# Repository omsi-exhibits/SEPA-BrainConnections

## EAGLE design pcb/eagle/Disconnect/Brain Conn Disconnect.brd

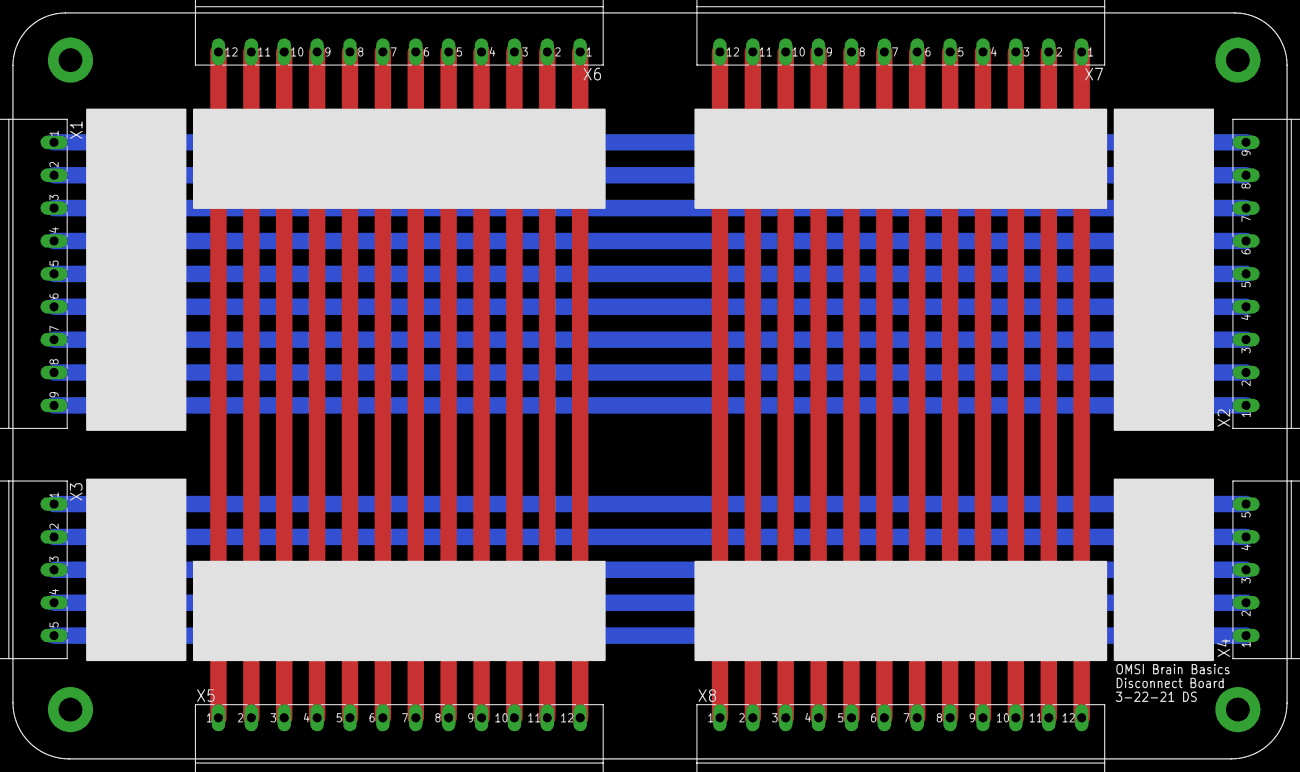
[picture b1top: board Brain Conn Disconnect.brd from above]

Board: 2 copper layers, 196.8 x 115.2 mm, 12 parts (0 on the bottom side), 38 nets.

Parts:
S1, S2, S3, S4: STANDOFF_ELECTRICAL144; STANDOFF_ELECTRICAL_144MILL_NORMAL_SCREW
X1, X2: MSTBA9
X3, X4: MSTBA5
X5, X6, X7, X8: MSTBA12

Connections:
unnamed: X3.1, X4.5
unnamed: X3.2, X4.4
unnamed: X3.3, X4.3
unnamed: X3.4, X4.2
unnamed: X3.5, X4.1
unnamed: X1.1, X2.9
unnamed: X1.2, X2.8
unnamed: X1.3, X2.7
unnamed: X1.4, X2.6
unnamed: X1.5, X2.5
unnamed: X1.6, X2.4
unnamed: X1.7, X2.3
unnamed: X1.8, X2.2
unnamed: X1.9, X2.1
unnamed: X5.12, X6.1
unnamed: X5.11, X6.2
unnamed: X5.10, X6.3
unnamed: X5.9, X6.4
unnamed: X5.8, X6.5
unnamed: X5.7, X6.6
unnamed: X5.6, X6.7
unnamed: X5.5, X6.8
unnamed: X5.4, X6.9
unnamed: X5.3, X6.10
unnamed: X5.2, X6.11
unnamed: X5.1, X6.12
unnamed: X7.1, X8.12
unnamed: X7.2, X8.11
unnamed: X7.3, X8.10
unnamed: X7.4, X8.9
unnamed: X7.5, X8.8
unnamed: X7.6, X8.7
unnamed: X7.7, X8.6
unnamed: X7.8, X8.5
unnamed: X7.9, X8.4
unnamed: X7.10, X8.3
unnamed: X7.11, X8.2
unnamed: X7.12, X8.1

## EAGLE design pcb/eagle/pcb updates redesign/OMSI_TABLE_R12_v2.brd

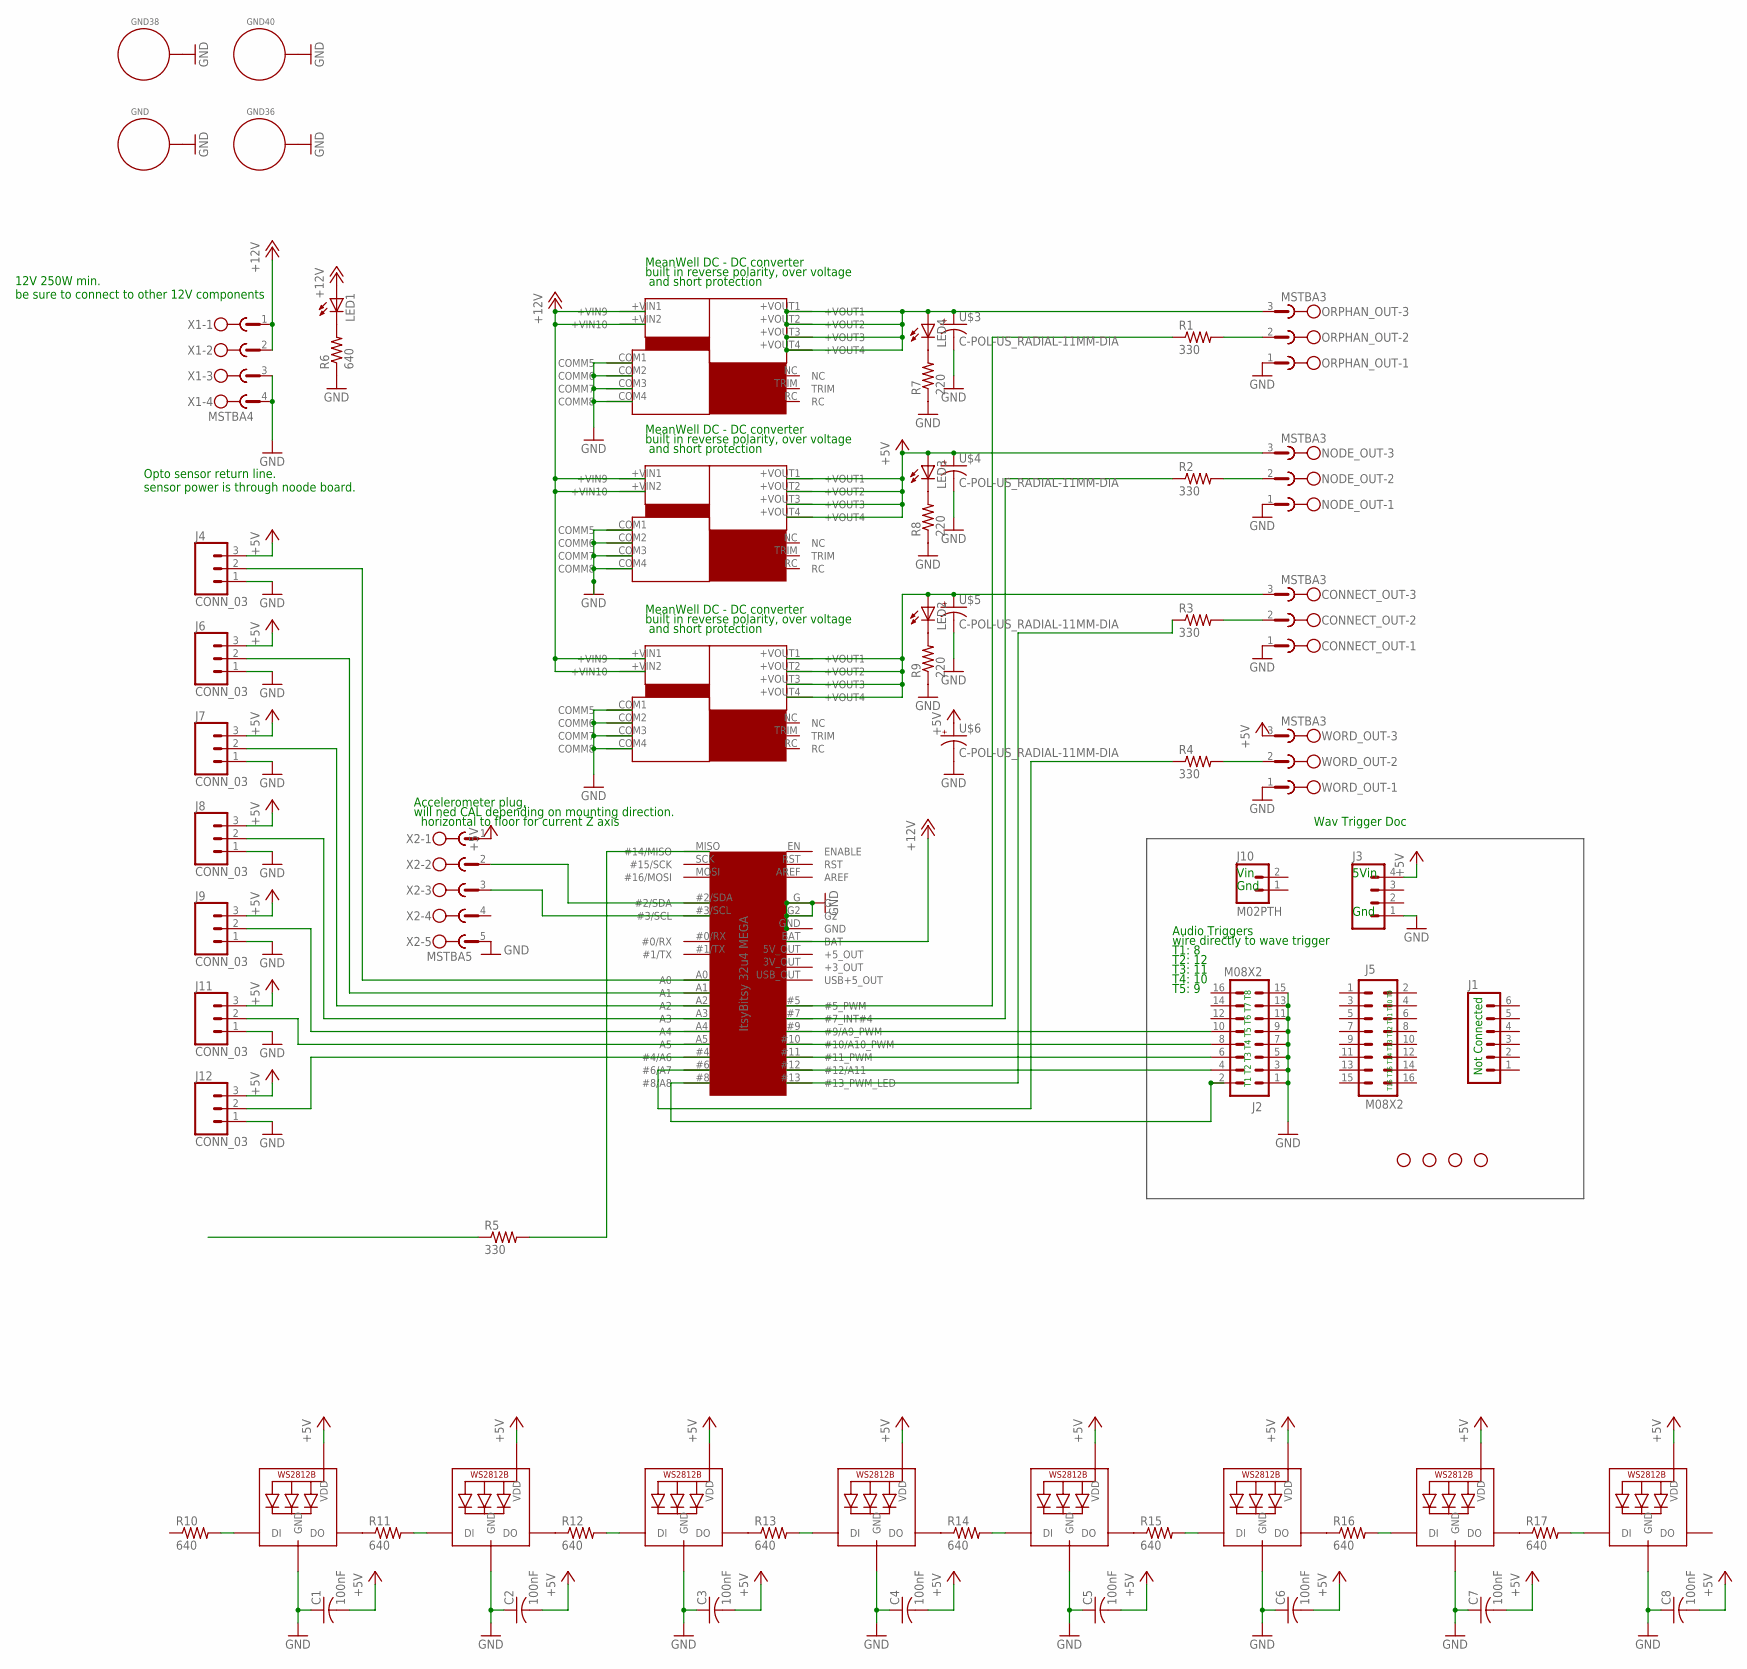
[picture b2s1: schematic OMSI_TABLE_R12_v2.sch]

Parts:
C1, C2, C3, C4, C5, C6, C7, C8: 100nF; C0805
CONNECT_OUT: MSTBA3
GND, GND36, GND38, GND40: STANDOFF_ELECTRICAL5-32; STANDOFF_ELECTRICAL_5_32
J1: M06SIP; 1X06
J2, J5: M08X2; 2X8
J3: M04PTH; 1X04
J4, J6, J7, J8, J9, J11, J12: CONN_03; 1X03_3.5MM_RA
J10: M02PTH; 1X02
LED1, LED2, LED3, LED4: LEDCHIPLED_1206; CHIPLED_1206
LED5, LED6, LED7, LED8, LED9, LED10, LED11, LED12: WS2812B; WS2812D-F5
MEANWELL_NID100_1, MEANWELL_NID100_2, MEANWELL_NID100_3: MEANWELL_NID100
NODE_OUT: MSTBA3
ORPHAN_OUT: MSTBA3
R1, R2, R3, R4, R5: 330; RESAD1176W63L850D250B
R6, R10, R11, R12, R13, R14, R15, R16, R17: 640; R0805
R7, R8, R9: 220; R0805
STANDOFF5, STANDOFF6, STANDOFF7, STANDOFF8: STAND-OFF
U$1: ITSYBITSY_32U4
U$3, U$4, U$5, U$6: C-POL-US_RADIAL-11MM-DIA; CAPPRD508W65D1000H1100B
WORD_OUT: MSTBA3
X1: MSTBA4
X2: MSTBA5

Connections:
+3_OUT: U$1.3V_OUT (+3_OUT)
+5V: C1.2, C2.2, C3.2, C4.2, C5.2, C6.2, C7.2, C8.2, J3.4, J4.3, J6.3, J7.3, J8.3, J9.3, J11.3, J12.3, LED3.A, LED5.P$2 (VDD), LED6.P$2 (VDD), LED7.P$2 (VDD), LED8.P$2 (VDD), LED9.P$2 (VDD), LED10.P$2 (VDD), LED11.P$2 (VDD), LED12.P$2 (VDD), MEANWELL_NID100_3.+VOUT1, MEANWELL_NID100_3.+VOUT2, MEANWELL_NID100_3.+VOUT3, MEANWELL_NID100_3.+VOUT4, NODE_OUT.3, U$4.1 (+), U$6.1 (+), WORD_OUT.3, X2.1
+5_OUT: U$1.5V_OUT (+5_OUT)
+12V: LED1.A, MEANWELL_NID100_1.+VIN1 (+VIN9), MEANWELL_NID100_1.+VIN2 (+VIN10), MEANWELL_NID100_2.+VIN1 (+VIN9), MEANWELL_NID100_2.+VIN2 (+VIN10), MEANWELL_NID100_3.+VIN1 (+VIN9), MEANWELL_NID100_3.+VIN2 (+VIN10), U$1.BAT, X1.1, X1.2
AREF: U$1.AREF
GND: C1.1, C2.1, C3.1, C4.1, C5.1, C6.1, C7.1, C8.1, CONNECT_OUT.1, GND.P1, GND36.P1, GND38.P1, GND40.P1, J2.1, J2.3, J2.5, J2.7, J2.9, J2.11, J2.13, J2.15, J3.1, J4.1, J6.1, J7.1, J8.1, J9.1, J11.1, J12.1, LED5.P$3 (GND), LED6.P$3 (GND), LED7.P$3 (GND), LED8.P$3 (GND), LED9.P$3 (GND), LED10.P$3 (GND), LED11.P$3 (GND), LED12.P$3 (GND), MEANWELL_NID100_1.COM1 (COMM5), MEANWELL_NID100_1.COM2 (COMM6), MEANWELL_NID100_1.COM3 (COMM7), MEANWELL_NID100_1.COM4 (COMM8), MEANWELL_NID100_2.COM1 (COMM5), MEANWELL_NID100_2.COM2 (COMM6), MEANWELL_NID100_2.COM3 (COMM7), MEANWELL_NID100_2.COM4 (COMM8), MEANWELL_NID100_3.COM1 (COMM5), MEANWELL_NID100_3.COM2 (COMM6), MEANWELL_NID100_3.COM3 (COMM7), MEANWELL_NID100_3.COM4 (COMM8), NODE_OUT.1, ORPHAN_OUT.1, R6.1, R7.1, R8.1, R9.1, U$1.G, U$1.G2, U$1.GND, U$3.2 (-), U$4.2 (-), U$5.2 (-), U$6.2 (-), WORD_OUT.1, X1.3, X1.4, X2.5
unnamed: LED4.A, MEANWELL_NID100_2.+VOUT1, MEANWELL_NID100_2.+VOUT2, MEANWELL_NID100_2.+VOUT3, MEANWELL_NID100_2.+VOUT4, ORPHAN_OUT.3, U$3.1 (+)
unnamed: U$1.#2/SDA, X2.2
unnamed: U$1.#3/SCL, X2.3
unnamed: J4.2, U$1.A0
unnamed: J6.2, U$1.A1
unnamed: J7.2, U$1.A2
unnamed: CONNECT_OUT.3, LED2.A, MEANWELL_NID100_1.+VOUT1, MEANWELL_NID100_1.+VOUT2, MEANWELL_NID100_1.+VOUT3, MEANWELL_NID100_1.+VOUT4, U$5.1 (+)
unnamed: J8.2, U$1.A3
unnamed: ORPHAN_OUT.2, R1.2
unnamed: R1.1, U$1.#5 (#5_PWM)
unnamed: NODE_OUT.2, R2.2
unnamed: J9.2, U$1.A4
unnamed: J11.2, U$1.A5
unnamed: J12.2, U$1.#4 (#4/A6)
unnamed: R2.1, U$1.#7 (#7_INT#4)
unnamed: CONNECT_OUT.2, R3.2
unnamed: R3.1, U$1.#13 (#13_PWM_LED)
unnamed: R4.2, WORD_OUT.2
unnamed: R4.1, U$1.#6 (#6/A7)
unnamed: J2.4, U$1.#12 (#12/A11)
unnamed: J2.6, U$1.#11 (#11_PWM)
unnamed: R5.2, U$1.MISO (#14/MISO)
unnamed: J2.8, U$1.#10 (#10/A10_PWM)
unnamed: J2.10, U$1.#9 (#9/A9_PWM)
unnamed: J2.2, U$1.#8 (#8/A8)
unnamed: LED1.C, R6.2
unnamed: LED4.C, R7.2
unnamed: LED3.C, R8.2
unnamed: LED2.C, R9.2
unnamed: LED6.P$4 (DI), R11.2
unnamed: LED5.P$1 (DO), R11.1
unnamed: LED5.P$4 (DI), R10.2
unnamed: LED7.P$4 (DI), R12.2
unnamed: LED6.P$1 (DO), R12.1
unnamed: LED8.P$4 (DI), R13.2
unnamed: LED7.P$1 (DO), R13.1
unnamed: LED9.P$4 (DI), R14.2
unnamed: LED8.P$1 (DO), R14.1
unnamed: LED10.P$4 (DI), R15.2
unnamed: LED9.P$1 (DO), R15.1
unnamed: LED11.P$4 (DI), R16.2
unnamed: LED10.P$1 (DO), R16.1
unnamed: LED12.P$4 (DI), R17.2
unnamed: LED11.P$1 (DO), R17.1
RST: U$1.RST
USB+5_OUT: U$1.USB_OUT (USB+5_OUT)

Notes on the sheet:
12V 250W min. be sure to connect to other 12V components
Opto sensor return line. sensor power is through noode board.
Accelerometer plug, will ned CAL depending on mounting direction. horizontal to floor for current Z axis
MeanWell DC - DC converter built in reverse polarity, over voltage and short protection
Audio Triggers wire directly to wave trigger T1: 8 T2: 12 T3: 11 T4: 10 T5: 9
Gnd
5Vin
Vin
T1 T2 T3 T4 T5 T6 T7 T8
T16 T15 T14 T13 T12 T11 T10 T9
Not Connected
Wav Trigger Doc

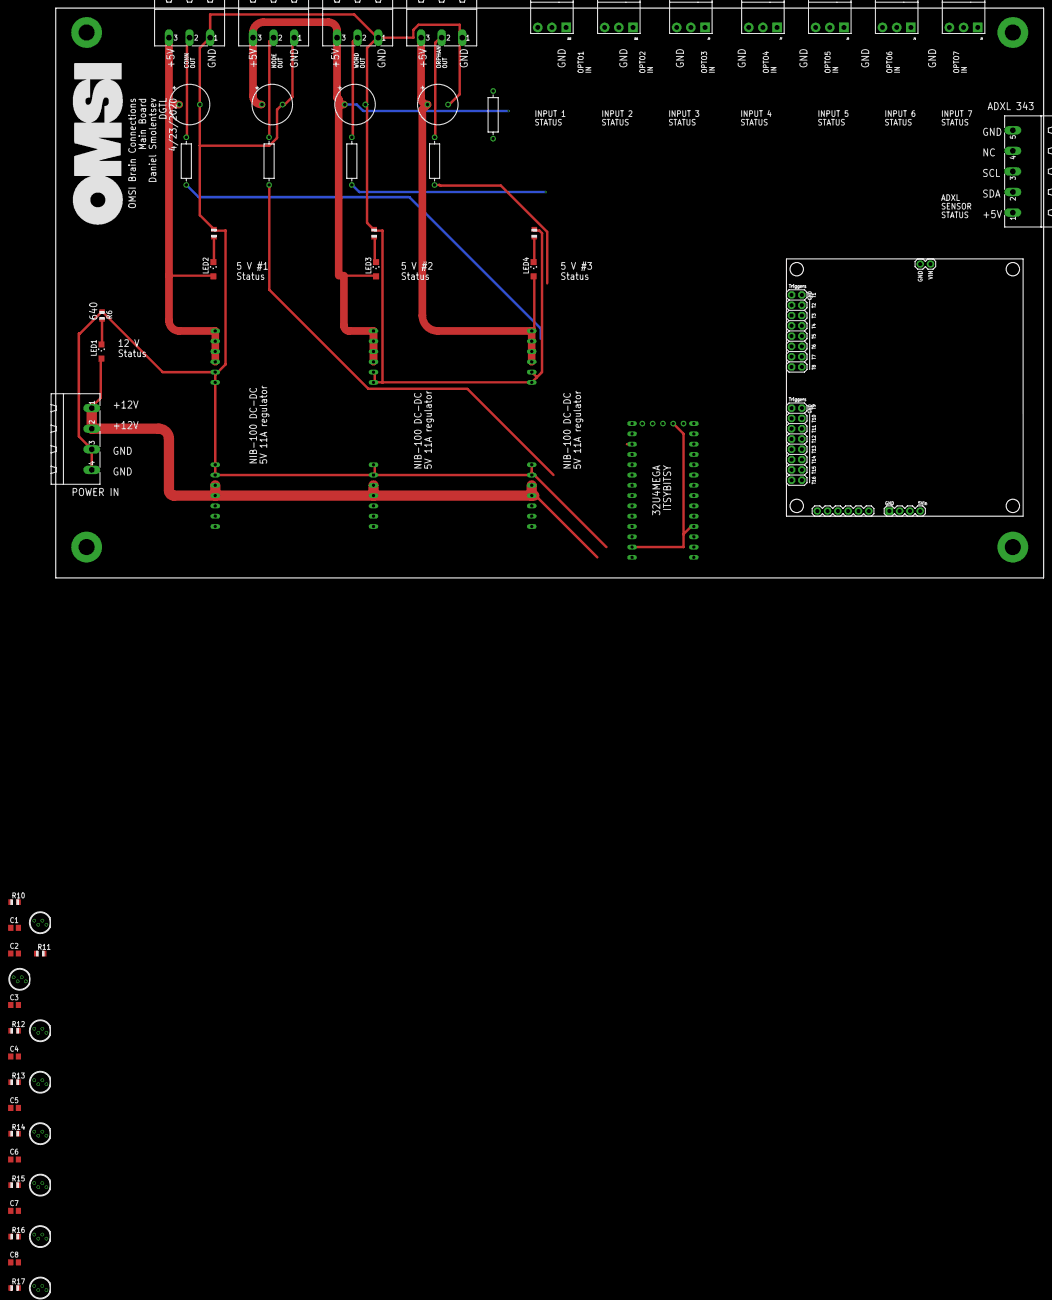
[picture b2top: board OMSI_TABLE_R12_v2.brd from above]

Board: 2 copper layers, 243.8 x 140.6 mm, 71 parts (0 on the bottom side), 47 nets.

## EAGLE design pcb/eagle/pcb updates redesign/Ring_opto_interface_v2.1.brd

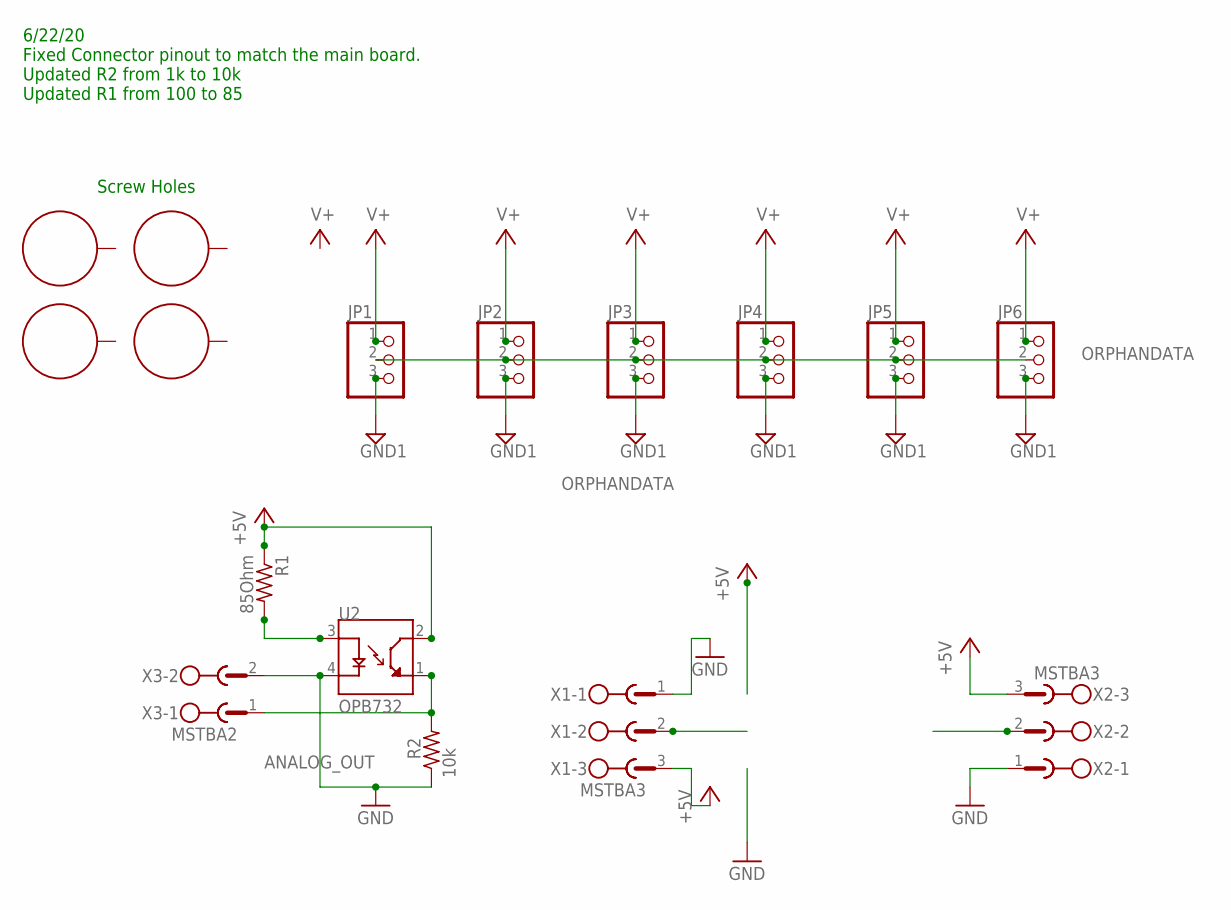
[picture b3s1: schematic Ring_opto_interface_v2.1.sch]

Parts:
H1, H2, H3, H4: STANDOFF_ELECTRICAL5-32; STANDOFF_ELECTRICAL_5_32
JP1, JP2, JP3, JP4, JP5, JP6: PINHD-1X3CB; 1X03-CLEANBIG
R1: 85Ohm; RESAD1176W63L850D250B
R2: 10k; RESAD1176W63L850D250B
U2: OPB732; OPTO_OPB732
X1, X2: MSTBA3
X3: MSTBA2

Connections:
+5V: R1.1, U2.2 (CT), X1.3, X2.3
ANALOG_OUT: R2.2, U2.1 (ET), X3.1
GND: R2.1, U2.4 (C), X1.1, X2.1, X3.2
GND1: JP1.3, JP2.3, JP3.3, JP4.3, JP5.3, JP6.3
unnamed: R1.2, U2.3 (A)
ORPHANDATA: JP1.2, JP2.2, JP3.2, JP4.2, JP5.2, JP6.2
V+: JP1.1, JP2.1, JP3.1, JP4.1, JP5.1, JP6.1

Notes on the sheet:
Screw Holes
6/22/20 Fixed Connector pinout to match the main board. Updated R2 from 1k to 10k Updated R1 from 100 to 85

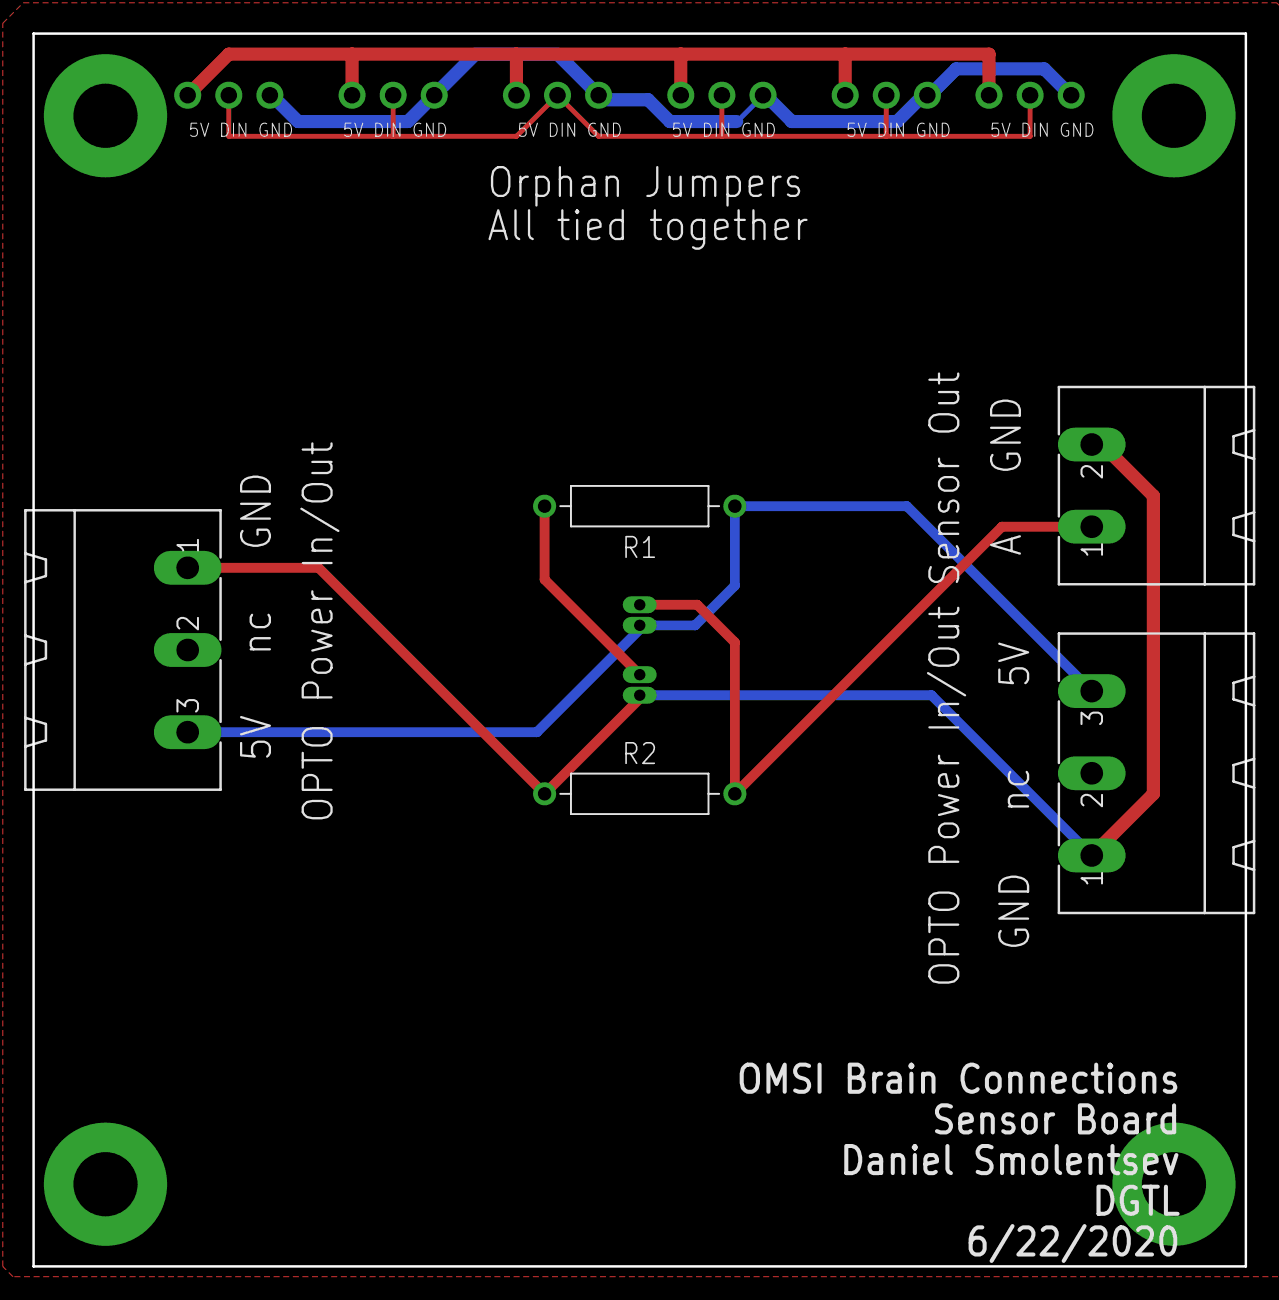
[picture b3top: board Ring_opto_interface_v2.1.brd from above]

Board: 2 copper layers, 74.9 x 76.2 mm, 16 parts (1 on the bottom side), 7 nets.

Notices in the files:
parts and their libraries:
SparkFun-Connectors: Licensing: CC v3.0 Share-Alike You are welcome to use this library for commercial purposes.
